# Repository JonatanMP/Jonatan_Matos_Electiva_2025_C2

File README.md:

# Jonatan_Matos_Electiva_2025_C2
HOLA PCB

_________________________________

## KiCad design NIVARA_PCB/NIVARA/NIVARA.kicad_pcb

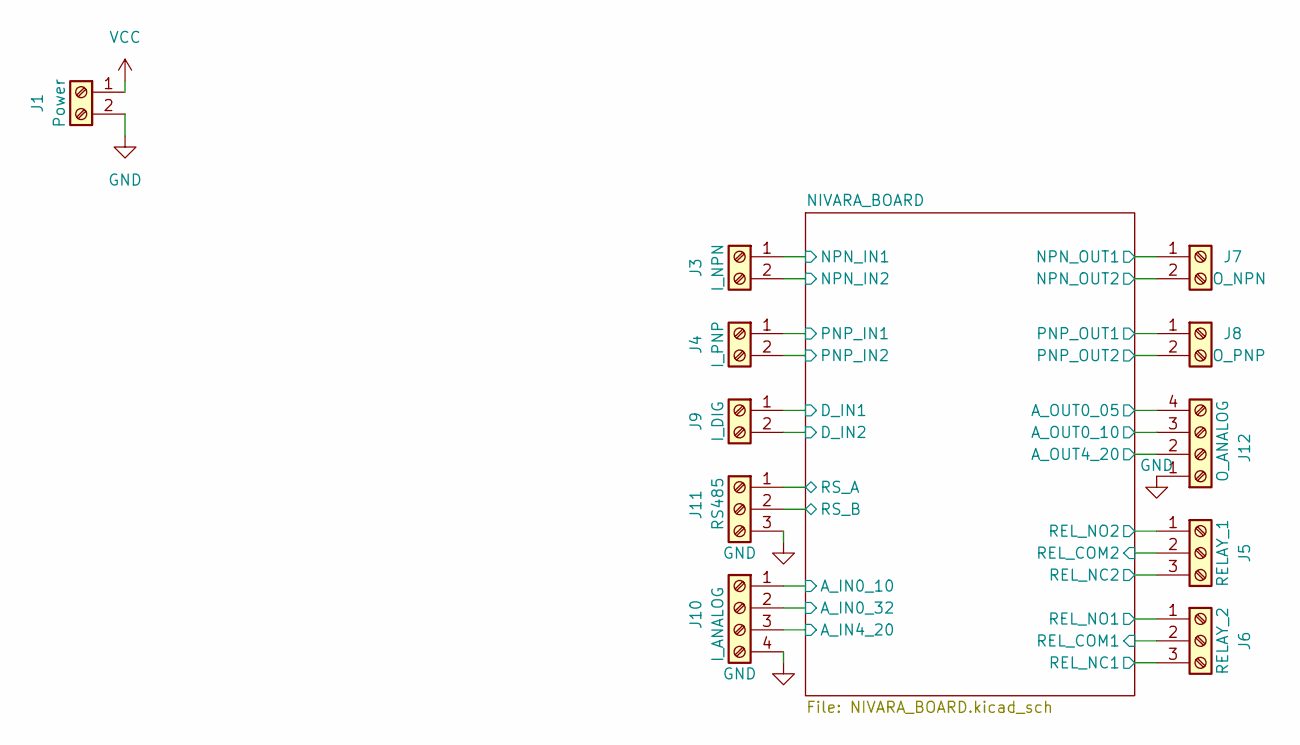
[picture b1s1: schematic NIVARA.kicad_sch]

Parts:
J1: Power; TerminalBlock_bornier-2_P5.08mm; PART NUMBERT DB128L-5.08-2P-OG-S
J3: I_NPN; TerminalBlock_bornier-2_P5.08mm; PART NUMBERT WJ500V-5.08-2P
J4: I_PNP; TerminalBlock_bornier-2_P5.08mm; PART NUMBERT WJ500V-5.08-2P
J5: RELAY_1; TerminalBlock_bornier-3_P5.08mm; PART NUMBERT WJ500V-5.08-3P
J6: RELAY_2; TerminalBlock_bornier-3_P5.08mm; PART NUMBERT WJ500V-5.08-3P
J7: O_NPN; TerminalBlock_bornier-2_P5.08mm; PART NUMBERT WJ500V-5.08-2P
J8: O_PNP; TerminalBlock_bornier-2_P5.08mm; PART NUMBERT WJ500V-5.08-2P
J9: I_DIG; TerminalBlock_bornier-2_P5.08mm; PART NUMBERT WJ500V-5.08-2P
J10: I_ANALOG; TerminalBlock_bornier-4_P5.08mm; PART NUMBERT WJ500V-5.08-4P
J11: RS485; TerminalBlock_bornier-3_P5.08mm; PART NUMBERT WJ500V-5.08-3P
J12: O_ANALOG; TerminalBlock_bornier-4_P5.08mm; PART NUMBERT WJ500V-5.08-4P

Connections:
/NIVARA_BOARD/A_IN0_10: J10.1; also elsewhere on the board
/NIVARA_BOARD/A_IN0_32: J10.2; also elsewhere on the board
/NIVARA_BOARD/A_IN4_20: J10.3; also elsewhere on the board
/NIVARA_BOARD/A_OUT0_05: J12.4; also elsewhere on the board
/NIVARA_BOARD/A_OUT0_10: J12.3; also elsewhere on the board
/NIVARA_BOARD/A_OUT4_20: J12.2; also elsewhere on the board
/NIVARA_BOARD/D_IN1: J9.1; also elsewhere on the board
/NIVARA_BOARD/D_IN2: J9.2; also elsewhere on the board
/NIVARA_BOARD/NPN_IN1: J3.1; also elsewhere on the board
/NIVARA_BOARD/NPN_IN2: J3.2; also elsewhere on the board
/NIVARA_BOARD/NPN_OUT1: J7.1; also elsewhere on the board
/NIVARA_BOARD/NPN_OUT2: J7.2; also elsewhere on the board
/NIVARA_BOARD/PNP_IN1: J4.1; also elsewhere on the board
/NIVARA_BOARD/PNP_IN2: J4.2; also elsewhere on the board
/NIVARA_BOARD/PNP_OUT1: J8.1; also elsewhere on the board
/NIVARA_BOARD/PNP_OUT2: J8.2; also elsewhere on the board
/NIVARA_BOARD/REL_COM1: J6.2; also elsewhere on the board
/NIVARA_BOARD/REL_COM2: J5.2; also elsewhere on the board
/NIVARA_BOARD/REL_NC1: J6.3; also elsewhere on the board
/NIVARA_BOARD/REL_NC2: J5.3; also elsewhere on the board
/NIVARA_BOARD/REL_NO1: J6.1; also elsewhere on the board
/NIVARA_BOARD/REL_NO2: J5.1; also elsewhere on the board
/NIVARA_BOARD/RS_A: J11.1; also elsewhere on the board
/NIVARA_BOARD/RS_B: J11.2; also elsewhere on the board
GND: J1.2, J10.4, J11.3, J12.1; also elsewhere on the board
VCC: J1.1; also elsewhere on the board

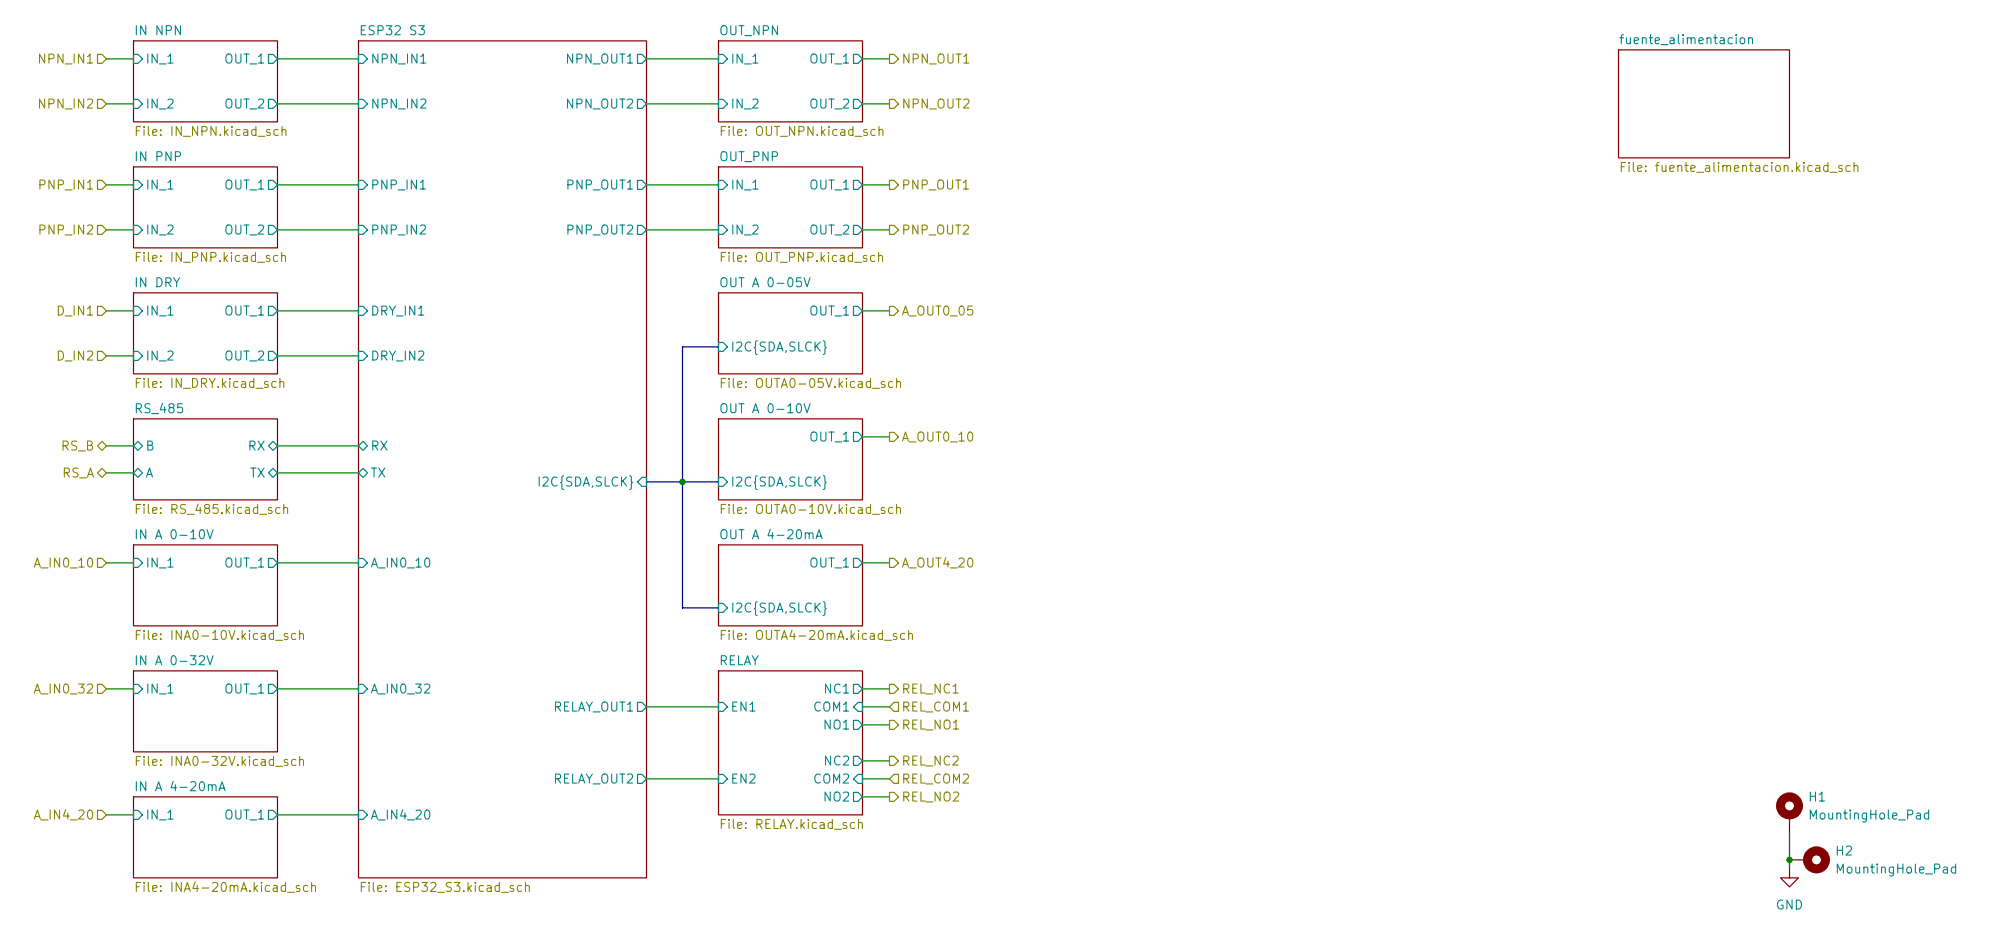
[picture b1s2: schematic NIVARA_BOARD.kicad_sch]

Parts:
H1, H2: MountingHole_Pad; MountingHole_2.2mm_M2_Pad_Via

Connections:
GND: H1.1, H2.1; also elsewhere on the board

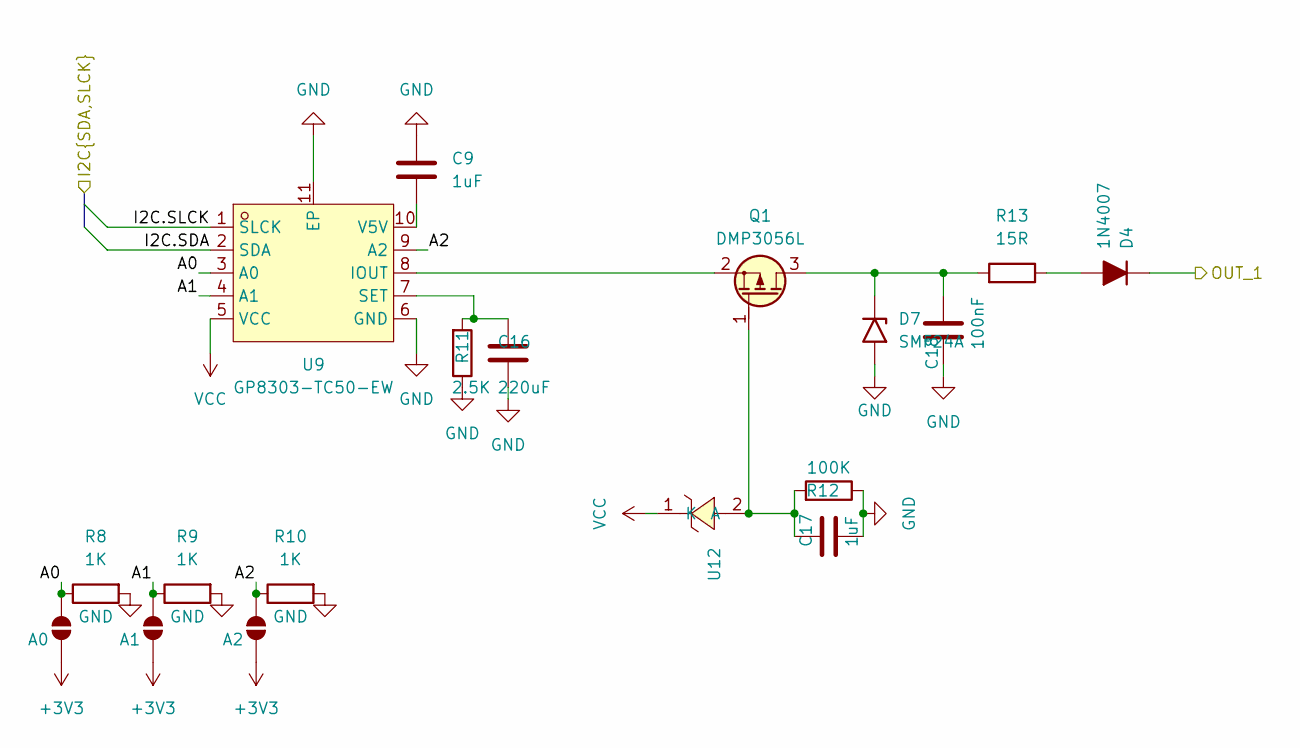
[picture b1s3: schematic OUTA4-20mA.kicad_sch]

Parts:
C9, C17: 1uF; C_0603_1608Metric; PART NUMBERT CL10A105KB8NNNC
C16: 220uF; C_0603_1608Metric; PART NUMBERT CC0603KRX7R9BB221
C18: 100nF; C_0603_1608Metric; PART NUMBERT CC0603KRX7R9BB104
D4: 1N4007; D_SOD-123F; PART NUMBERT 1N4007W 46MIL
D7: SMF24A; D_SMF
JP2: A0; SolderJumper-2_P1.3mm_Open_RoundedPad1.0x1.5mm
JP3: A1; SolderJumper-2_P1.3mm_Open_RoundedPad1.0x1.5mm
JP4: A2; SolderJumper-2_P1.3mm_Open_RoundedPad1.0x1.5mm
Q1: DMP3056L; SOT-23
R8, R9, R10: 1K; R_0603_1608Metric; PART NUMBERT RC0603FR-071KL
R11: 2.5K; R_0603_1608Metric; PART NUMBERT FRQ0805F2501TS
R12: 100K; R_0603_1608Metric; PART NUMBERT RC0603FR-07100KL
R13: 15R; R_1206_3216Metric; PART NUMBERT RC1206FR-0715RL
U9: GP8303-TC50-EW; ESOP-10_L4.9-W3.9-P1.00-LS6.1-BL-EP; LCSC Part C3445809
U12: ZMM12V_C5345999; LL-34_L3.5-W1.5-RD-2; LCSC Part C5345999

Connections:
+3V3: JP2.1 (A), JP3.1 (A), JP4.1 (A); also elsewhere on the board
/NIVARA_BOARD/A_OUT4_20: D4.1 (K); also elsewhere on the board
/NIVARA_BOARD/ESP32 S3/I2C.SDA: U9.2 (SDA); also elsewhere on the board
/NIVARA_BOARD/ESP32 S3/I2C.SLCK: U9.1 (SLCK); also elsewhere on the board
/NIVARA_BOARD/OUT A 4-20mA/A0: JP2.2 (B), R8.2, U9.3 (A0)
/NIVARA_BOARD/OUT A 4-20mA/A1: JP3.2 (B), R9.2, U9.4 (A1)
/NIVARA_BOARD/OUT A 4-20mA/A2: JP4.2 (B), R10.2, U9.9 (A2)
GND: C9.1, C16.2, C17.2, C18.1, D7.2 (A2), R8.1, R9.1, R10.1, R11.2, R12.2, U9.6 (GND), U9.11 (EP); also elsewhere on the board
unnamed: D4.2 (A), R13.2
unnamed: C18.2, D7.1 (A1), Q1.3 (D), R13.1
unnamed: C17.1, Q1.1 (G), R12.1, U12.2 (A)
unnamed: Q1.2 (S), U9.8 (IOUT)
unnamed: C16.1, R11.1, U9.7 (SET)
unnamed: C9.2, U9.10 (V5V)
VCC: U9.5 (VCC), U12.1 (K); also elsewhere on the board

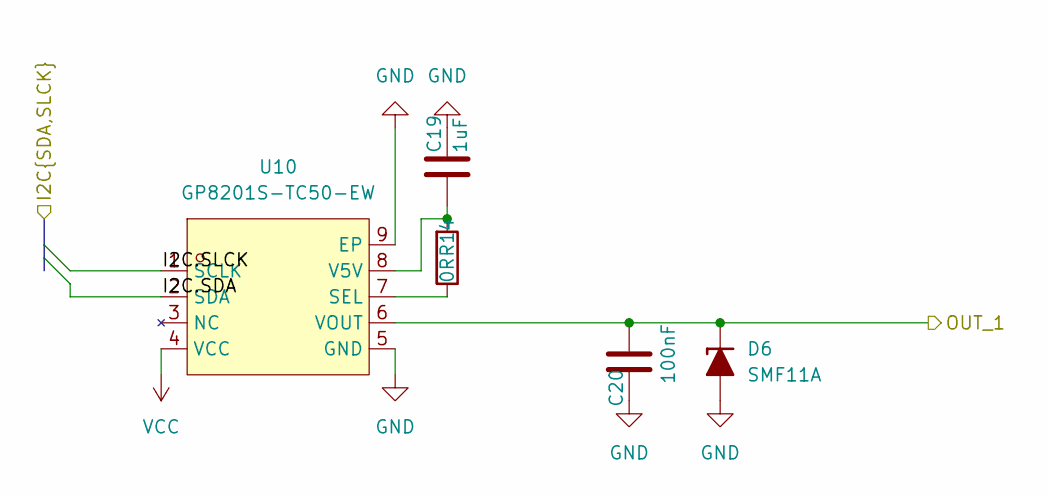
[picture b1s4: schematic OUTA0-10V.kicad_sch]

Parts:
C19: 1uF; C_0603_1608Metric; PART NUMBERT CL10A105KB8NNNC
C20: 100nF; C_0603_1608Metric; PART NUMBERT CC0603KRX7R9BB104
D6: SMF11A; D_SOD-123F
R14: 0R; R_0603_1608Metric; PART NUMBERT RC0603FR-070RL
U10: GP8201S-TC50-EW; ESOP-8_L4.9-W3.9-P1.27-LS6.0-BL-EP; LCSC Part C5240058

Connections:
/NIVARA_BOARD/A_OUT0_10: C20.2, D6.1 (K), U10.6 (VOUT); also elsewhere on the board
/NIVARA_BOARD/ESP32 S3/I2C.SDA: U10.2 (SDA); also elsewhere on the board
/NIVARA_BOARD/ESP32 S3/I2C.SLCK: U10.1 (SCLK); also elsewhere on the board
GND: C19.1, C20.1, D6.2 (A), U10.5 (GND), U10.9 (EP); also elsewhere on the board
unnamed: R14.2, U10.7 (SEL)
unnamed: C19.2, R14.1, U10.8 (V5V)
VCC: U10.4 (VCC); also elsewhere on the board

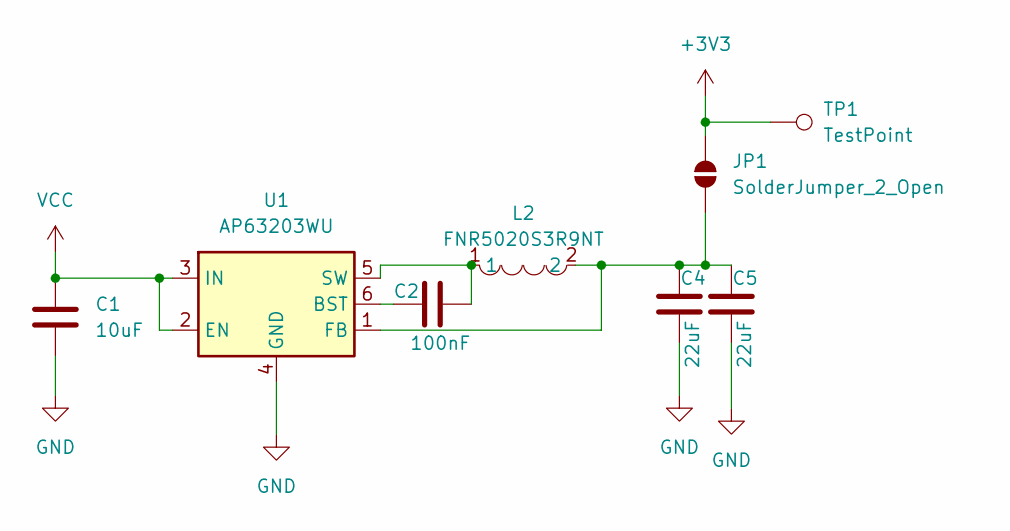
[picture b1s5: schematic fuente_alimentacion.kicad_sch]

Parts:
C1: 10uF; C_1206_3216Metric; PART NUMBERT CL31A106KBHNNNE
C2: 100nF; C_0603_1608Metric; PART NUMBERT CC0603KRX7R9BB104
C4, C5: 22uF; C_0603_1608Metric; PART NUMBERT CL10A226MP8NUNE
JP1: SolderJumper_2_Open; SolderJumper-2_P1.3mm_Open_RoundedPad1.0x1.5mm
L2: FNR5020S3R9NT; IND-SMD_L5.0-W5.0_FNR50XXS; LCSC Part C167928
TP1: TestPoint; TestPoint_THTPad_D1.0mm_Drill0.5mm
U1: AP63203WU; TSOT-23-6; PART NUMBERT AP63203WU-7

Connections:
+3V3: JP1.2 (B), TP1.1; also elsewhere on the board
GND: C1.2, C4.2, C5.2, U1.4 (GND); also elsewhere on the board
unnamed: C4.1, C5.1, JP1.1 (A), L2.2, U1.1 (FB)
unnamed: C2.1, U1.6 (BST)
unnamed: C2.2, L2.1, U1.5 (SW)
VCC: C1.1, U1.2 (EN), U1.3 (IN); also elsewhere on the board

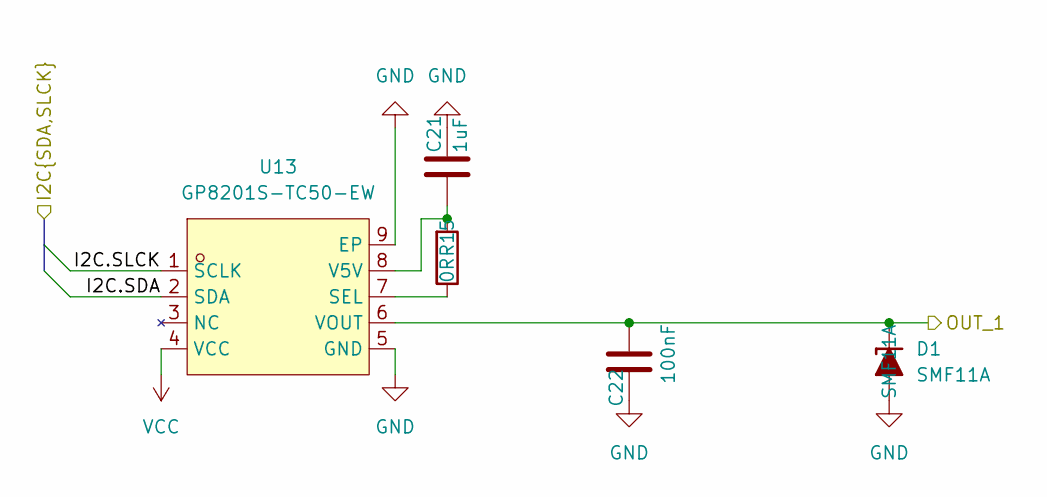
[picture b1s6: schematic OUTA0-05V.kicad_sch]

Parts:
C21: 1uF; C_0603_1608Metric; PART NUMBERT CL10A105KB8NNNC
C22: 100nF; C_0603_1608Metric; PART NUMBERT CC0603KRX7R9BB104
D1: SMF11A; D_SOD-123F; PART NUMBERT SMF11A
R15: 0R; R_0603_1608Metric; PART NUMBERT RC0603FR-070RL
U13: GP8201S-TC50-EW; ESOP-8_L4.9-W3.9-P1.27-LS6.0-BL-EP; LCSC Part C5240058

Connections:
/NIVARA_BOARD/A_OUT0_05: C22.2, D1.1 (K), U13.6 (VOUT); also elsewhere on the board
/NIVARA_BOARD/ESP32 S3/I2C.SDA: U13.2 (SDA); also elsewhere on the board
/NIVARA_BOARD/ESP32 S3/I2C.SLCK: U13.1 (SCLK); also elsewhere on the board
GND: C21.1, C22.1, D1.2 (A), U13.5 (GND), U13.9 (EP); also elsewhere on the board
unnamed: R15.2, U13.7 (SEL)
unnamed: C21.2, R15.1, U13.8 (V5V)
VCC: U13.4 (VCC); also elsewhere on the board

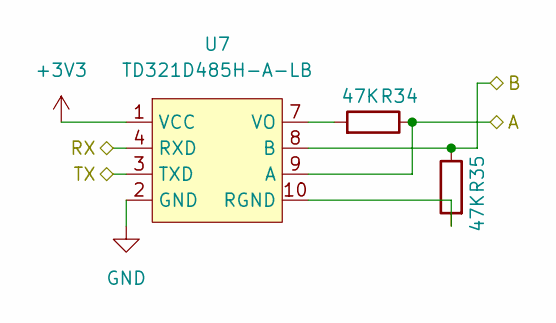
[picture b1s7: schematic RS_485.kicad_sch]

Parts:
R34, R35: 47K; R_0603_1608Metric
U7: TD321D485H-A-LB

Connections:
+3V3: U7.1 (VCC); also elsewhere on the board
/NIVARA_BOARD/ESP32 S3/RX: U7.4 (RXD); also elsewhere on the board
/NIVARA_BOARD/ESP32 S3/TX: U7.3 (TXD); also elsewhere on the board
/NIVARA_BOARD/RS_A: R34.2, U7.9 (A); also elsewhere on the board
/NIVARA_BOARD/RS_B: R35.2, U7.8 (B); also elsewhere on the board
GND: U7.2 (GND); also elsewhere on the board
unnamed: R35.1, U7.10 (RGND)
unnamed: R34.1, U7.7 (VO)

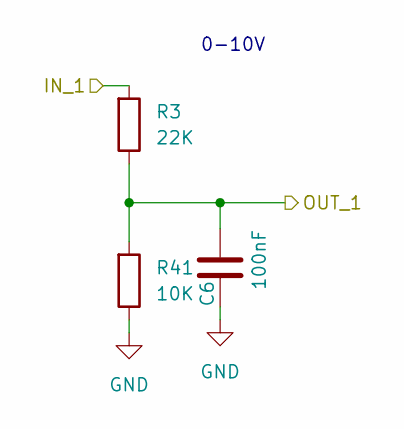
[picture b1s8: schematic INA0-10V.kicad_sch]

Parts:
C6: 100nF; C_0603_1608Metric; PART NUMBERT CC0603KRX7R9BB104
R3: 22K; R_0603_1608Metric; PART NUMBERT RC0603FR-0722KL
R41: 10K; R_0603_1608Metric

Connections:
/NIVARA_BOARD/A_IN0_10: R3.1; also elsewhere on the board
/NIVARA_BOARD/ESP32 S3/A_IN0_10: C6.2, R3.2, R41.1; also elsewhere on the board
GND: C6.1, R41.2; also elsewhere on the board

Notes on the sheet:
0-10V

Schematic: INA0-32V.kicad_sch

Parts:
C7: 100nF; C_0603_1608Metric; PART NUMBERT CC0603KRX7R9BB104
R6: 22K; R_0603_1608Metric; PART NUMBERT RC0603FR-0722KL
R18: 2.5K; R_0603_1608Metric; PART NUMBERT FRQ0805F2501TS

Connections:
/NIVARA_BOARD/A_IN0_32: R6.1; also elsewhere on the board
/NIVARA_BOARD/ESP32 S3/A_IN0_32: C7.2, R6.2, R18.1; also elsewhere on the board
GND: C7.1, R18.2; also elsewhere on the board

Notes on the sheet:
0-32V

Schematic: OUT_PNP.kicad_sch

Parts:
IC1: ITS5215; Infineon_PG-DSO-12-9_ThermalVias
R1, R2: 15K; R_0603_1608Metric; PART NUMBERT RC0603FR-0715KL

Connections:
+3V3: R1.1, R2.1; also elsewhere on the board
/NIVARA_BOARD/ESP32 S3/PNP_OUT1: IC1.2 (IN1); also elsewhere on the board
/NIVARA_BOARD/ESP32 S3/PNP_OUT2: IC1.4 (IN2); also elsewhere on the board
/NIVARA_BOARD/PNP_OUT1: IC1.8 (OUT2); also elsewhere on the board
/NIVARA_BOARD/PNP_OUT2: IC1.10 (OUT1); also elsewhere on the board
GND: IC1.1 (GND); also elsewhere on the board
unnamed: IC1.3 (ST1), R2.2
unnamed: IC1.5 (ST2), R1.2
VCC: IC1.6 (VBB), IC1.12 (VBB), IC1.13 (VBB); also elsewhere on the board

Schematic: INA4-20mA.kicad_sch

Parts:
C8: 100nF; C_0603_1608Metric; PART NUMBERT CC0603KRX7R9BB104
R7: 150R; R_0603_1608Metric; PART NUMBERT RC0603FR-07150RL

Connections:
/NIVARA_BOARD/A_IN4_20: C8.2, R7.1; also elsewhere on the board
GND: C8.1, R7.2; also elsewhere on the board

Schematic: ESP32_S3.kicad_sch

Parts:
C23, C24, C25: 100nF; C_0603_1608Metric; PART NUMBERT CC0603KRX7R9BB104
R42, R45: 2.5K; R_0603_1608Metric; PART NUMBERT FRQ0805F2501TS
R46, R47: 10K; R_0603_1608Metric
U11: ESP32-S3-WROOM-1

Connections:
+3V3: C23.2, C24.2, R42.1, R45.1, R46.1, R47.1, U11.2 (3V3); also elsewhere on the board
/NIVARA_BOARD/A_IN4_20: U11.39 (GPIO1/TOUCH1/ADC1_CH0); also elsewhere on the board
/NIVARA_BOARD/ESP32 S3/A_IN0_10: U11.22 (GPIO14/TOUCH14/ADC2_CH3/FSPIWP/FSPIDQS/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); also elsewhere on the board
/NIVARA_BOARD/ESP32 S3/A_IN0_32: U11.38 (GPIO2/TOUCH2/ADC1_CH1); also elsewhere on the board
/NIVARA_BOARD/ESP32 S3/BOOT: R47.2, U11.27 (GPIO0/BOOT)
/NIVARA_BOARD/ESP32 S3/DRY_IN1: U11.21 (GPIO13/TOUCH13/ADC2_CH2/FSPIQ/FSPIIO7/S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); also elsewhere on the board
/NIVARA_BOARD/ESP32 S3/DRY_IN2: U11.20 (GPIO12/TOUCH12/ADC2_CH1/FSPICLK/FSPIIO6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); also elsewhere on the board
/NIVARA_BOARD/ESP32 S3/EN: C25.2, R46.2, U11.3 (EN)
/NIVARA_BOARD/ESP32 S3/I2C.SDA: R42.2, U11.4 (GPIO4/TOUCH4/ADC1_CH3); also elsewhere on the board
/NIVARA_BOARD/ESP32 S3/I2C.SLCK: R45.2, U11.5 (GPIO5/TOUCH5/ADC1_CH4); also elsewhere on the board
/NIVARA_BOARD/ESP32 S3/NPN_IN1: U11.26 (GPIO45); also elsewhere on the board
/NIVARA_BOARD/ESP32 S3/NPN_IN2: U11.25 (GPIO48/SPICLK_N/SUBSPICLK_N_DIFF); also elsewhere on the board
/NIVARA_BOARD/ESP32 S3/NPN_OUT1: U11.10 (GPIO17/U1TXD/ADC2_CH6); also elsewhere on the board
/NIVARA_BOARD/ESP32 S3/NPN_OUT2: U11.11 (GPIO18/U1RXD/ADC2_CH7/CLK_OUT3); also elsewhere on the board
/NIVARA_BOARD/ESP32 S3/PNP_IN1: U11.24 (GPIO47/SPICLK_P/SUBSPICLK_P_DIFF); also elsewhere on the board
/NIVARA_BOARD/ESP32 S3/PNP_IN2: U11.23 (GPIO21); also elsewhere on the board
/NIVARA_BOARD/ESP32 S3/PNP_OUT1: U11.8 (GPIO15/U0RTS/ADC2_CH4/XTAL_32K_P); also elsewhere on the board
/NIVARA_BOARD/ESP32 S3/PNP_OUT2: U11.7 (GPIO7/TOUCH7/ADC1_CH6); also elsewhere on the board
/NIVARA_BOARD/ESP32 S3/RELAY_OUT1: U11.6 (GPIO6/TOUCH6/ADC1_CH5); also elsewhere on the board
/NIVARA_BOARD/ESP32 S3/RELAY_OUT2: U11.9 (GPIO16/U0CTS/ADC2_CH5/XTAL_32K_N); also elsewhere on the board
/NIVARA_BOARD/ESP32 S3/RX: U11.18 (GPIO10/TOUCH10/ADC1_CH9/FSPICS0/FSPIIO4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); also elsewhere on the board
/NIVARA_BOARD/ESP32 S3/TX: U11.19 (GPIO11/TOUCH11/ADC2_CH0/FSPID/FSPIIO5/S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); also elsewhere on the board
GND: C23.1, C24.1, C25.1, U11.1 (GND), U11.40 (GND), U11.41 (GND); also elsewhere on the board

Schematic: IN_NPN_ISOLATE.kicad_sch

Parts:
C11: 1uF; C_0603_1608Metric; PART NUMBERT CL10A105KB8NNNC
LED6: LED_0603_Green; LED_0603_1608Metric; PART NUMBERT XL-1608UOC-06
R5: 1K; R_0603_1608Metric; PART NUMBERT RC0603FR-071KL
R21: 10K; R_0603_1608Metric
R22: 50R; R_0603_1608Metric; PART NUMBERT RT0603BRE0750RL
TP7: TestPoint; TestPoint_THTPad_D1.0mm_Drill0.5mm
U4: AT3H4A-CUH-S; SSOP-4_L2.7-W4.6-P1.27-LS7.0-TL; PART NUMBERT AT3H4A-CUH-S; LCSC Part C20612634

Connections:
+3V3: R21.1, R22.1; also elsewhere on the board
/NIVARA_BOARD/ESP32 S3/NPN_IN2: C11.1, LED6.1 (K), R21.2, TP7.1, U4.4 (C); also elsewhere on the board
/NIVARA_BOARD/NPN_IN2: R5.2; also elsewhere on the board
GND: C11.2, U4.2 (C/A), U4.3 (E); also elsewhere on the board
unnamed: LED6.2 (A), R22.2
unnamed: R5.1, U4.1 (A/C)

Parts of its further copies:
C10: 1uF; C_0603_1608Metric; PART NUMBERT CL10A105KB8NNNC
LED5: LED_0603_Green; LED_0603_1608Metric; PART NUMBERT XL-1608UOC-06
R4: 1K; R_0603_1608Metric; PART NUMBERT RC0603FR-071KL
R19: 10K; R_0603_1608Metric
R20: 50R; R_0603_1608Metric; PART NUMBERT RT0603BRE0750RL
TP6: TestPoint; TestPoint_THTPad_D1.0mm_Drill0.5mm
U2: AT3H4A-CUH-S; SSOP-4_L2.7-W4.6-P1.27-LS7.0-TL; PART NUMBERT AT3H4A-CUH-S; LCSC Part C20612634

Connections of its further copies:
+3V3: R19.1, R20.1; also elsewhere on the board
/NIVARA_BOARD/ESP32 S3/NPN_IN1: C10.1, LED5.1 (K), R19.2, TP6.1, U2.4 (C); also elsewhere on the board
/NIVARA_BOARD/NPN_IN1: R4.2; also elsewhere on the board
GND: C10.2, U2.2 (C/A), U2.3 (E); also elsewhere on the board
unnamed: LED5.2 (A), R20.2
unnamed: R4.1, U2.1 (A/C)

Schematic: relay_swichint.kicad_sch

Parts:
D3: 1N4007; D_SOD-123F; PART NUMBERT 1N4007W 46MIL
Q4: PMBT3904; SOT-23; PART NUMBERT PMBT3904,215
R43: 22K; R_0603_1608Metric; PART NUMBERT RC0603FR-0722KL
R44: 10K; R_0603_1608Metric
RLY3: SRD-24VDC-SL-C; RELAY-TH_SRD-XXVDC-XL-C; PART NUMBERT SRD-24VDC-SL-C; LCSC Part C15840

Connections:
/NIVARA_BOARD/ESP32 S3/RELAY_OUT1: R43.1; also elsewhere on the board
/NIVARA_BOARD/REL_COM1: RLY3.5; also elsewhere on the board
/NIVARA_BOARD/REL_NC1: RLY3.3; also elsewhere on the board
/NIVARA_BOARD/REL_NO1: RLY3.2; also elsewhere on the board
GND: Q4.2 (E), R44.1; also elsewhere on the board
unnamed: D3.2 (A), Q4.3 (C), RLY3.4
unnamed: Q4.1 (B), R43.2, R44.2
VCC: D3.1 (K), RLY3.1; also elsewhere on the board

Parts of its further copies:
D2: 1N4007; D_SOD-123F; PART NUMBERT 1N4007W 46MIL
Q2: PMBT3904; SOT-23; PART NUMBERT PMBT3904,215
R32: 22K; R_0603_1608Metric; PART NUMBERT RC0603FR-0722KL
R33: 10K; R_0603_1608Metric
RLY2: SRD-24VDC-SL-C; RELAY-TH_SRD-XXVDC-XL-C; PART NUMBERT SRD-24VDC-SL-C; LCSC Part C15840

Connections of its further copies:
/NIVARA_BOARD/ESP32 S3/RELAY_OUT2: R32.1; also elsewhere on the board
/NIVARA_BOARD/REL_COM2: RLY2.5; also elsewhere on the board
/NIVARA_BOARD/REL_NC2: RLY2.3; also elsewhere on the board
/NIVARA_BOARD/REL_NO2: RLY2.2; also elsewhere on the board
GND: Q2.2 (E), R33.1; also elsewhere on the board
unnamed: D2.2 (A), Q2.3 (C), RLY2.4
unnamed: Q2.1 (B), R32.2, R33.2
VCC: D2.1 (K), RLY2.1; also elsewhere on the board

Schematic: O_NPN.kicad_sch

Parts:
R31: 1K; R_0603_1608Metric; PART NUMBERT RC0603FR-071KL
R36: 22K; R_0603_1608Metric; PART NUMBERT RC0603FR-0722KL
U14: ZXMS6004FFQTA; SOT-23F_L2.9-W1.8-P0.95-LS2.4-BR

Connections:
/NIVARA_BOARD/ESP32 S3/NPN_OUT2: R31.2; also elsewhere on the board
/NIVARA_BOARD/NPN_OUT2: U14.3 (D); also elsewhere on the board
GND: R36.2, U14.2 (S); also elsewhere on the board
unnamed: R31.1, R36.1, U14.1 (IN)

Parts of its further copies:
R23: 1K; R_0603_1608Metric; PART NUMBERT RC0603FR-071KL
R30: 22K; R_0603_1608Metric; PART NUMBERT RC0603FR-0722KL
U15: ZXMS6004FFQTA; SOT-23F_L2.9-W1.8-P0.95-LS2.4-BR

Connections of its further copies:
/NIVARA_BOARD/ESP32 S3/NPN_OUT1: R23.2; also elsewhere on the board
/NIVARA_BOARD/NPN_OUT1: U15.3 (D); also elsewhere on the board
GND: R30.2, U15.2 (S); also elsewhere on the board
unnamed: R23.1, R30.1, U15.1 (IN)

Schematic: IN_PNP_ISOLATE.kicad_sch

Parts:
C13: 1uF; C_0603_1608Metric; PART NUMBERT CL10A105KB8NNNC
LED8: LED_0603_Green; LED_0603_1608Metric; PART NUMBERT XL-1608UOC-06
R25: 1K; R_0603_1608Metric; PART NUMBERT RC0603FR-071KL
R27, R29: 10K; R_0603_1608Metric
TP10: TestPoint; TestPoint_THTPad_D1.0mm_Drill0.5mm
U6: AT3H4A-CUH-S; SSOP-4_L2.7-W4.6-P1.27-LS7.0-TL; PART NUMBERT AT3H4A-CUH-S; LCSC Part C20612634

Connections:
+3V3: R27.1, R29.1; also elsewhere on the board
/NIVARA_BOARD/ESP32 S3/PNP_IN2: C13.1, LED8.1 (K), R27.2, TP10.1, U6.4 (C); also elsewhere on the board
/NIVARA_BOARD/PNP_IN2: R25.2; also elsewhere on the board
GND: C13.2, U6.3 (E); also elsewhere on the board
unnamed: LED8.2 (A), R29.2
unnamed: R25.1, U6.1 (A/C)
VCC: U6.2 (C/A); also elsewhere on the board

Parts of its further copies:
C12: 1uF; C_0603_1608Metric; PART NUMBERT CL10A105KB8NNNC
LED7: LED_0603_Green; LED_0603_1608Metric; PART NUMBERT XL-1608UOC-06
R24: 1K; R_0603_1608Metric; PART NUMBERT RC0603FR-071KL
R26, R28: 10K; R_0603_1608Metric
TP9: TestPoint; TestPoint_THTPad_D1.0mm_Drill0.5mm
U5: AT3H4A-CUH-S; SSOP-4_L2.7-W4.6-P1.27-LS7.0-TL; PART NUMBERT AT3H4A-CUH-S; LCSC Part C20612634

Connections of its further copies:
+3V3: R26.1, R28.1; also elsewhere on the board
/NIVARA_BOARD/ESP32 S3/PNP_IN1: C12.1, LED7.1 (K), R26.2, TP9.1, U5.4 (C); also elsewhere on the board
/NIVARA_BOARD/PNP_IN1: R24.2; also elsewhere on the board
GND: C12.2, U5.3 (E); also elsewhere on the board
unnamed: LED7.2 (A), R28.2
unnamed: R24.1, U5.1 (A/C)
VCC: U5.2 (C/A); also elsewhere on the board

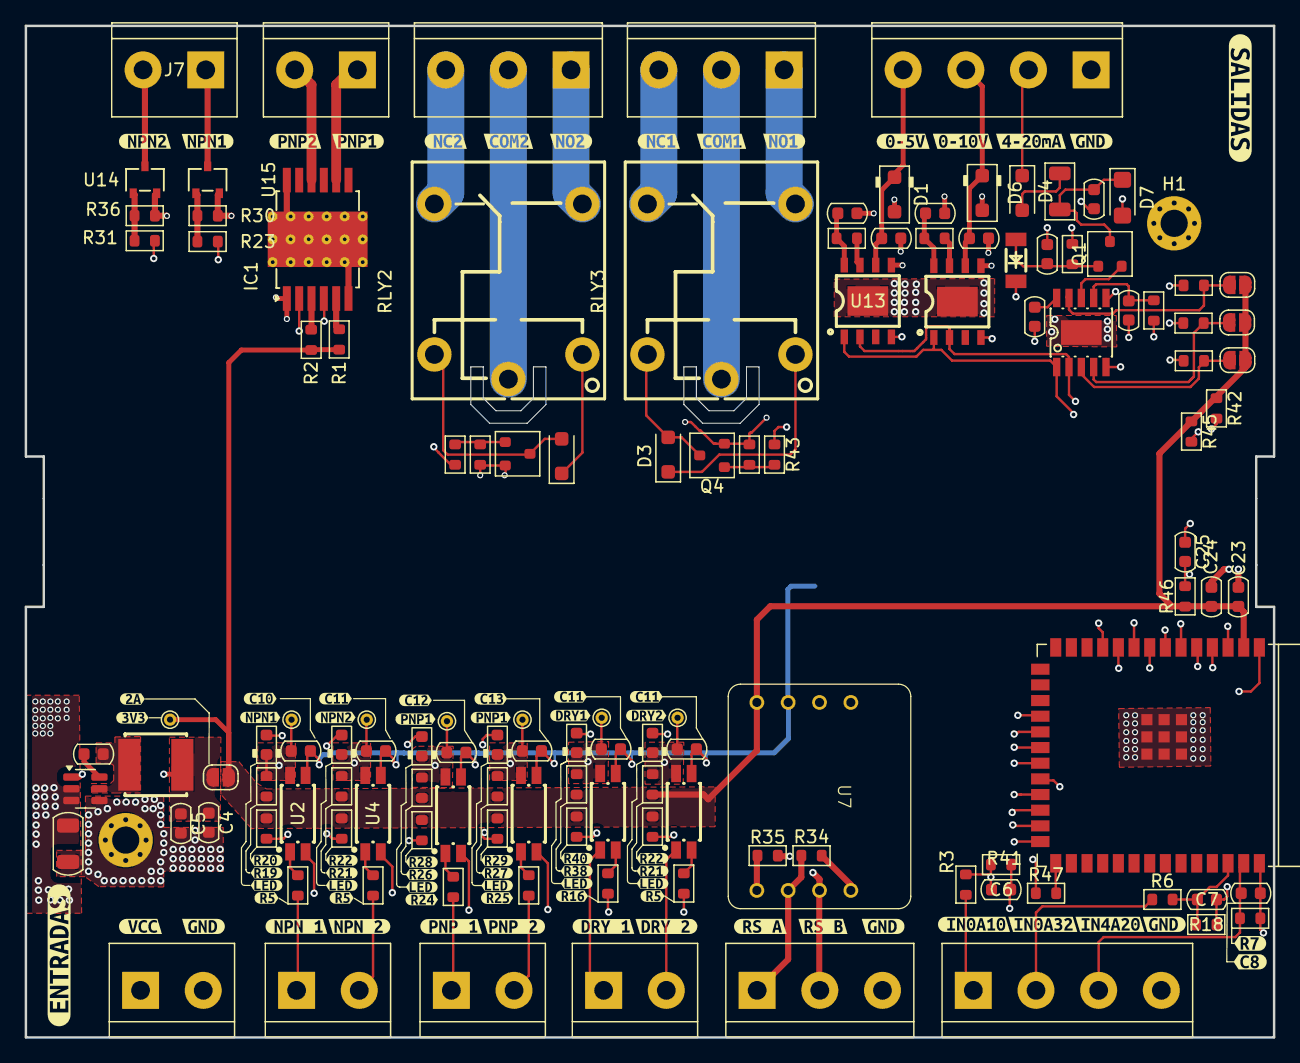
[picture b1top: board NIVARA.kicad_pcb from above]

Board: 4 copper layers, 101.2 x 82.0 mm, 200 parts (0 on the bottom side), 85 nets.

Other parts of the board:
C14, C15: 1uF; C_0603_1608Metric
LED9, LED10: LED_0603_Green; LED_0603_1608Metric
R16, R17: 1K; R_0603_1608Metric
R37, R38: 10K; R_0603_1608Metric
R39, R40: 50R; R_0603_1608Metric
TP11, TP12: TestPoint; TestPoint_THTPad_D1.0mm_Drill0.5mm
U3, U8: AT3H4A-CUH-S; SSOP-4_L2.7-W4.6-P1.27-LS7.0-TL
kibuzzard-68A4ACEC: G***; kibuzzard-68A4ACEC
kibuzzard-68A4AD1D: G***; kibuzzard-68A4AD1D
kibuzzard-68A4AD43: G***; kibuzzard-68A4AD43
kibuzzard-68A4AD55: G***; kibuzzard-68A4AD55
kibuzzard-68A4AE0E: G***; kibuzzard-68A4AE0E
kibuzzard-68A4AE1F: G***; kibuzzard-68A4AE1F
kibuzzard-68A4AE2A: G***; kibuzzard-68A4AE2A
kibuzzard-68A4AE4D: G***; kibuzzard-68A4AE4D
kibuzzard-68A4AE5E: G***; kibuzzard-68A4AE5E
kibuzzard-68A4AE56: G***; kibuzzard-68A4AE56
kibuzzard-68A4AF5B: G***; kibuzzard-68A4AF5B
kibuzzard-68A4AF27: G***; kibuzzard-68A4AF27
kibuzzard-68A4AF38: G***; kibuzzard-68A4AF38
kibuzzard-68A4AF50: G***; kibuzzard-68A4AF50
kibuzzard-68A4B67A: G***; kibuzzard-68A4B67A
kibuzzard-68A4B644: G***; kibuzzard-68A4B644
kibuzzard-68A851A1: G***; kibuzzard-68A851A1
kibuzzard-68A85187: G***; kibuzzard-68A85187
kibuzzard-68A85197: G***; kibuzzard-68A85197
kibuzzard-688D0FD4: G***; kibuzzard-688D0FD4
kibuzzard-688D4BEB: G***; kibuzzard-688D4BEB
kibuzzard-688D4BF9: G***; kibuzzard-688D4BF9
kibuzzard-688D4C3C: G***; kibuzzard-688D4C3C
kibuzzard-688D4C4D: G***; kibuzzard-688D4C4D
kibuzzard-688D4C16: G***; kibuzzard-688D4C16
kibuzzard-688D10E8: G***; kibuzzard-688D10E8
kibuzzard-688D10FC: G***; kibuzzard-688D10FC
kibuzzard-688D1008: G***; kibuzzard-688D1008
kibuzzard-6886A0F4: G***; kibuzzard-6886A0F4
kibuzzard-6886A071, kibuzzard-6886A071#2: G***; kibuzzard-6886A071
kibuzzard-6886A148, kibuzzard-6886A148#2, kibuzzard-6886A148#3: G***; kibuzzard-6886A148
kibuzzard-6886AD53: G***; kibuzzard-6886AD53
kibuzzard-6886AD61: G***; kibuzzard-6886AD61
kibuzzard-6886ADA1: G***; kibuzzard-6886ADA1
kibuzzard-6886ADC6: G***; kibuzzard-6886ADC6
kibuzzard-6886ADE0: G***; kibuzzard-6886ADE0
kibuzzard-6886ADF2: G***; kibuzzard-6886ADF2
kibuzzard-6886AE03: G***; kibuzzard-6886AE03
kibuzzard-6886AE16: G***; kibuzzard-6886AE16
kibuzzard-6886AE38: G***; kibuzzard-6886AE38
kibuzzard-6886AE62: G***; kibuzzard-6886AE62
kibuzzard-6886CB2B: G***; kibuzzard-6886CB2B
kibuzzard-6886CB54: G***; kibuzzard-6886CB54
kibuzzard-68857B38: G***; kibuzzard-68857B38
kibuzzard-68868B65: G***; kibuzzard-68868B65
kibuzzard-68868CAC: G***; kibuzzard-68868CAC
kibuzzard-68868CE5: G***; kibuzzard-68868CE5
kibuzzard-68868D86: G***; kibuzzard-68868D86
kibuzzard-68868DBB: G***; kibuzzard-68868DBB
kibuzzard-68868E7D: G***; kibuzzard-68868E7D
kibuzzard-68868E8A: G***; kibuzzard-68868E8A
kibuzzard-68868F64: G***; kibuzzard-68868F64
kibuzzard-68868F72: G***; kibuzzard-68868F72
kibuzzard-68869F01, kibuzzard-68869F01#2, kibuzzard-68869F01#3: G***; kibuzzard-68869F01
kibuzzard-688671E8: G***; kibuzzard-688671E8
kibuzzard-688672FE: G***; kibuzzard-688672FE
kibuzzard-688673E6, kibuzzard-688673E6#2: G***; kibuzzard-688673E6
kibuzzard-6886740D, kibuzzard-6886740D#2: G***; kibuzzard-6886740D
kibuzzard-68867375, kibuzzard-68867375#2, kibuzzard-68867375#3, kibuzzard-68867375#4, kibuzzard-68867375#5, kibuzzard-68867375#6: G***; kibuzzard-68867375

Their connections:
+3V3: R37.1, R38.1, R39.1, R40.1; also elsewhere on the board
/NIVARA_BOARD/D_IN1: U8.1 (A/C); also elsewhere on the board
/NIVARA_BOARD/D_IN2: U3.1 (A/C); also elsewhere on the board
/NIVARA_BOARD/ESP32 S3/DRY_IN1: C15.1, LED10.1 (K), R38.2, TP12.1, U8.4 (C); also elsewhere on the board
/NIVARA_BOARD/ESP32 S3/DRY_IN2: C14.1, LED9.1 (K), R37.2, TP11.1, U3.4 (C); also elsewhere on the board
GND: C14.2, C15.2, R16.1, R17.1, U3.3 (E), U8.3 (E); also elsewhere on the board
unnamed: LED9.2 (A), R39.2
unnamed: LED10.2 (A), R40.2
unnamed: R17.2, U3.2 (C/A)
unnamed: R16.2, U8.2 (C/A)

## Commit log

2025-05-30 Se creo una carpeta para cada programa
2025-06-07 base del case del plc
2025-06-08 regitas de un lado
2025-06-09 AVANCE EN BASE PLC DE SOLID EDGE
2025-06-09 AVANCE BASE_PLC
2025-06-11 Agrego DXF 2D, Termino 3D FrC, creacion Kicad
    Frc = freecad
    Se agrego el DXF tanto de la base como del case en freecad.
    Se termino el diseño 3D de Freecad, agregando pequeños detalles faltantes.
    Se empezo el proyecto de kicad, agregando las delimitaciones fisicas necesarias.
2025-06-13 agregar cosas faltantes
2025-06-13 giagramas faltantes
2025-06-14 kicad
2025-06-29 avance en diagramas
2025-07-09 AVANCES
    se realizaron avances con las entradas NPN, PNP. tambien se realizaron avances con las salidas de RELAYS
2025-07-09 se agrego diodo de proteccion a los relays
2025-07-09 se agregaron partnumbers
2025-07-09 RS_485 ADD MODULE
2025-07-11 ACTUALIZACION
2025-07-14 se agrego hirarchical de esp32 s3
2025-07-16 avance
2025-07-17 SALIDAS DE VOLTAJE Y CORRIENTE
2025-07-28 Se organizaron componentes en el area de PCB
2025-08-01 organizando componentes en la pcb
2025-08-08 ACTUALIZACION DE SALIDAS NPN Y PNP
2025-08-19 arreglo del desastre que tenia con las salidas PNP
2025-08-22 se extendio GND
2025-08-22 ruteo de salidas
2025-08-22 RUTEO ENTRADAS
